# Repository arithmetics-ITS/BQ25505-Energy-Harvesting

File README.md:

# Breakout Board: BQ25505 ultra low-power energy harvester with battery management and autonomous power multiplexing
## Description

The bq25505 device is specifically designed to efficiently extract the microwatts (μW) to miliwatts (mW) of power generated from a variety of DC energy harvesting, high-impedance sources like photovoltaic (solar) or thermal electric generators (TEGs) without collapsing those sources. The batterymanagement features of the bq25505 ensure that a secondary rechargeable battery is not overcharged by this extracted power, with voltage boosted, nor depleted beyond safe limits by a system load. The
integrated multiplexer gate drivers autonomously switch the system load to a primary nonrechargeable battery if the secondary battery voltage falls below the user-defined VBAT_OK threshold.

## Features

- Texas Instruments BQ25505
- Designed for solar applications with MPPT
- 2x Dual, P-Channel, ChipFET 20 V, 4.1 A for primary and secondary battery switching
- 2x LEDs to visualize the currently used battery (PRI or SEC)

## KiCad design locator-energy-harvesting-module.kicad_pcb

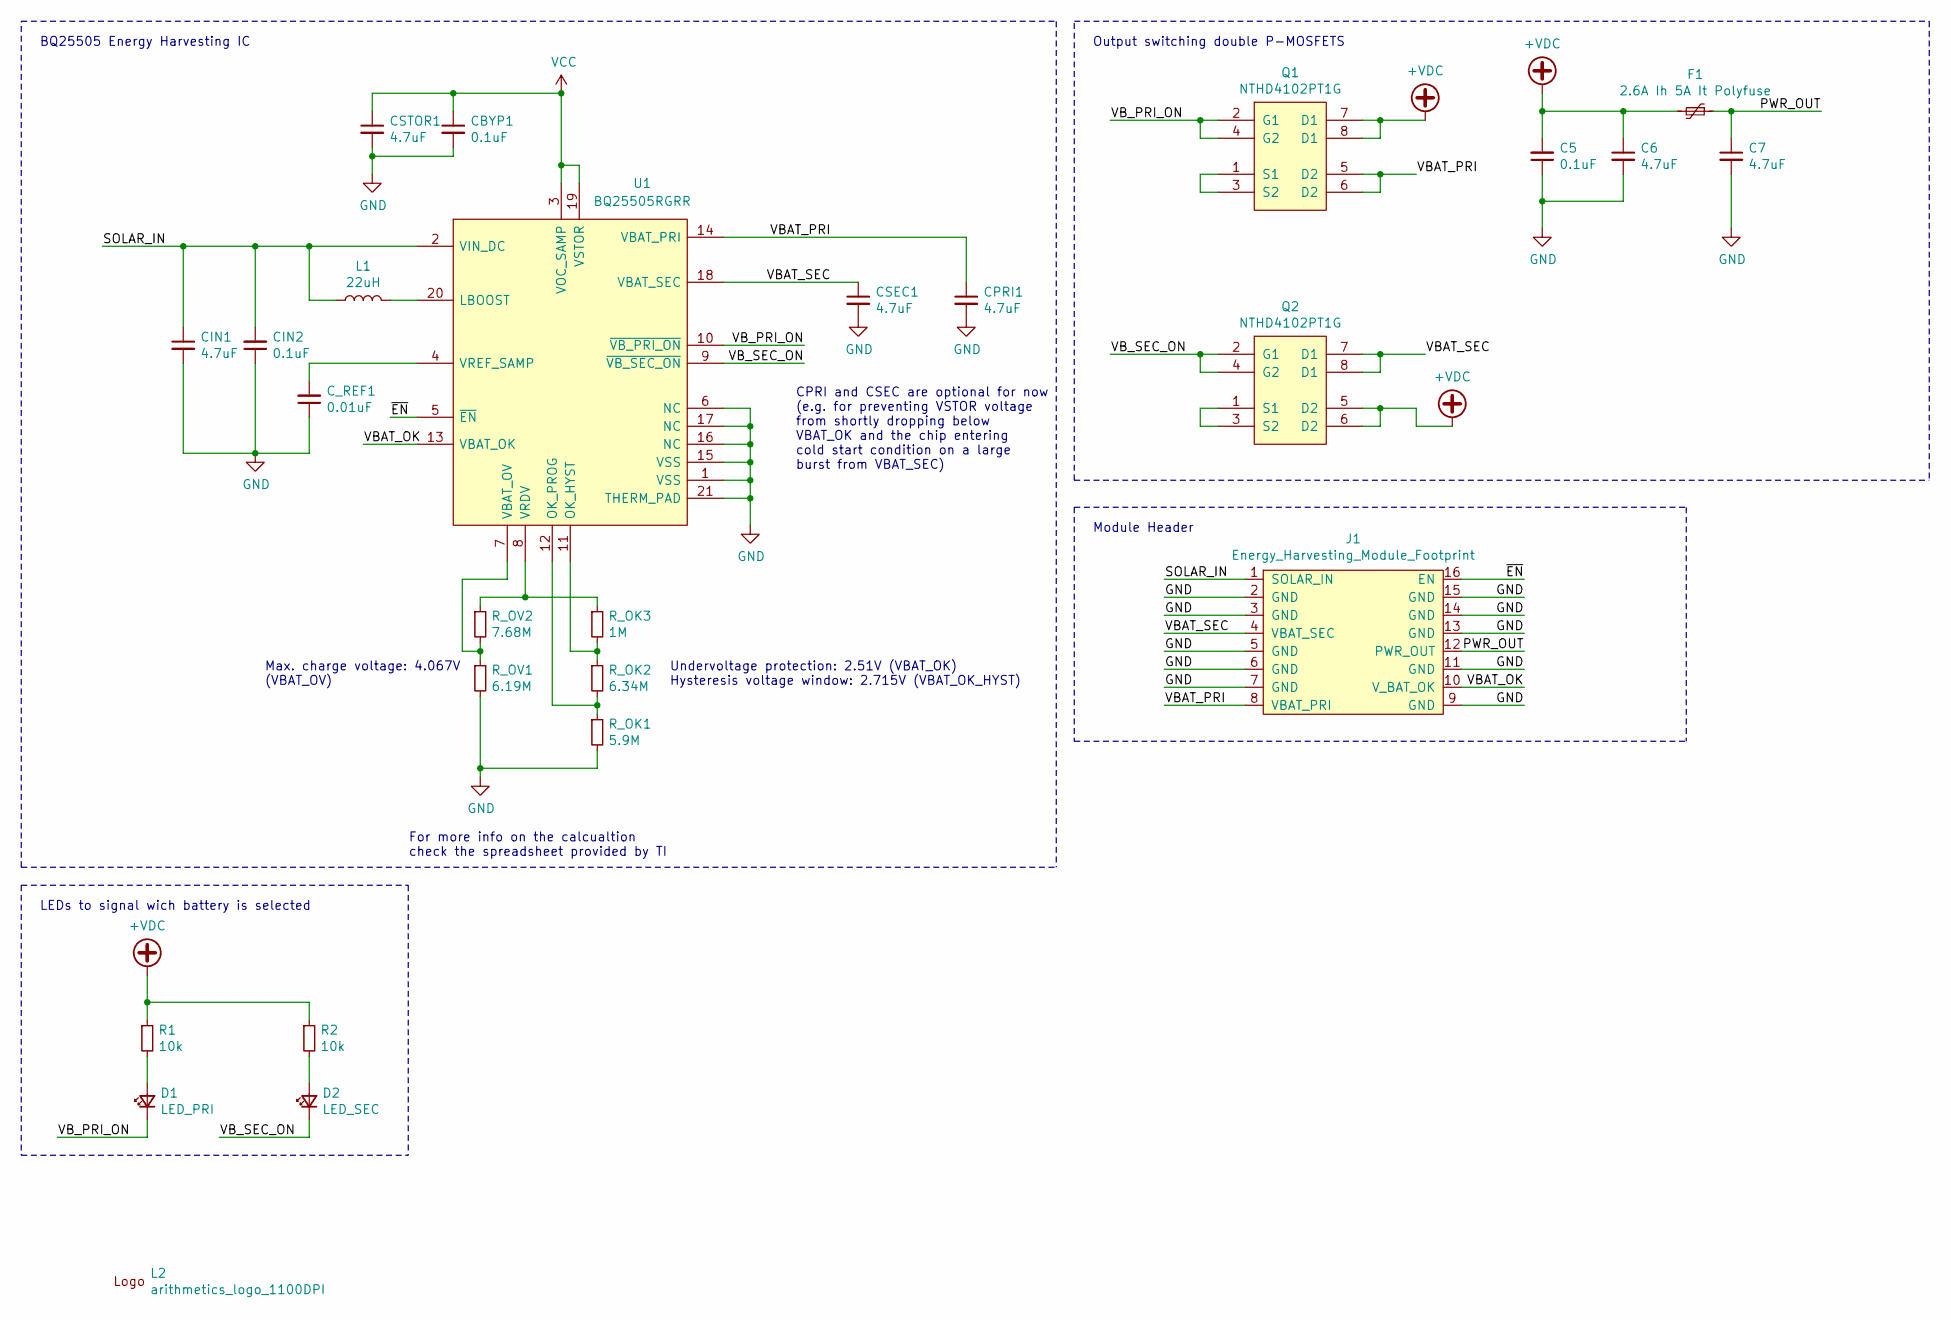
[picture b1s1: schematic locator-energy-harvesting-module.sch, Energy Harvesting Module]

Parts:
C5: 0.1uF; C_0603_1608Metric; MPN C0603X104J4RECAUTO
C6, C7: 4.7uF; C_0603_1608Metric; MPN C1608X5R1C475K080AC
CBYP1: 0.1uF; C_0603_1608Metric; MPN C0603X104J4RECAUTO
CIN1: 4.7uF; C_0603_1608Metric; MPN C1608X5R1C475K080AC
CIN2: 0.1uF; C_0603_1608Metric; MPN C0603X104J4RECAUTO
CPRI1: 4.7uF; C_0603_1608Metric; MPN C1608X5R1C475K080AC
CSEC1: 4.7uF; C_0603_1608Metric; MPN C1608X5R1C475K080AC
CSTOR1: 4.7uF; C_0603_1608Metric; MPN C1608X5R1C475K080AC
C_REF1: 0.01uF; C_0603_1608Metric; MPN GRM1885C1H103JA01D
D1: LED_PRI; LED_0603_1608Metric; MPN LS L29K-G1H2-1-Z
D2: LED_SEC; LED_0603_1608Metric; MPN LS L29K-G1H2-1-Z
F1: 2.6A Ih 5A It Polyfuse; Fuse_1812_4532Metric_Castellated; MPN 0ZCG0260FF2C
J1: Energy_Harvesting_Module_Footprint
L1: 22uH; L_Coilcraft_LPS4018; MPN LPS4018-223MRB
L2: arithmetics_logo_1100DPI; logo_1100_DPI
Q1, Q2: NTHD4102PT1G; NTHD4102P_ChipFET_CASE_1206A; MPN NTHD4102PT1G
R1, R2: 10k; R_0603_1608Metric; MPN AC0603JR-0710KL
R_OK1: 5.9M; R_0603_1608Metric; MPN CRCW06035M90FKEA
R_OK2: 6.34M; R_0603_1608Metric; MPN CRCW06036M34FKEA
R_OK3: 1M; R_0603_1608Metric; MPN AC0603FR-071ML
R_OV1: 6.19M; R_0603_1608Metric; MPN CRCW06036M19FKEA
R_OV2: 7.68M; R_0603_1608Metric; MPN CRCW06037M68FKEA
U1: BQ25505RGRR; BQ25505; MPN BQ25505RGRR

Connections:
+VDC: C5.2, C6.1, F1.2, Q1.7 (D1), Q1.8 (D1), Q2.5 (D2), Q2.6 (D2), R1.1, R2.1
/PWR_OUT: C7.1, F1.1, J1.12 (PWR_OUT)
/SOLAR_IN: CIN1.1, CIN2.2, J1.1 (SOLAR_IN), L1.1, U1.2 (VIN_DC)
/VBAT_OK: J1.10 (V_BAT_OK), U1.13 (VBAT_OK)
/VBAT_PRI: CPRI1.1, J1.8 (VBAT_PRI), Q1.5 (D2), Q1.6 (D2), U1.14 (VBAT_PRI)
/VBAT_SEC: CSEC1.1, J1.4 (VBAT_SEC), Q2.7 (D1), Q2.8 (D1), U1.18 (VBAT_SEC)
/VB_PRI_ON: D1.1 (K), Q1.2 (G1), Q1.4 (G2), U1.10 (~VB_PRI_ON)
/VB_SEC_ON: D2.1 (K), Q2.2 (G1), Q2.4 (G2), U1.9 (~VB_SEC_ON)
/~EN: J1.16 (EN), U1.5 (~EN)
GND: C5.1, C6.2, C7.2, CBYP1.2, CIN1.2, CIN2.1, CPRI1.2, CSEC1.2, CSTOR1.2, C_REF1.1, J1.2 (GND), J1.3 (GND), J1.5 (GND), J1.6 (GND), J1.7 (GND), J1.9 (GND), J1.11 (GND), J1.13 (GND), J1.14 (GND), J1.15 (GND), R_OK1.2, R_OV1.2, U1.1 (VSS), U1.6 (NC), U1.15 (VSS), U1.16 (NC), U1.17 (NC), U1.21 (THERM_PAD)
unnamed: C_REF1.2, U1.4 (VREF_SAMP)
unnamed: D1.2 (A), R1.2
unnamed: D2.2 (A), R2.2
unnamed: L1.2, U1.20 (LBOOST)
unnamed: Q1.1 (S1), Q1.3 (S2)
unnamed: Q2.1 (S1), Q2.3 (S2)
unnamed: R_OK1.1, R_OK2.2, U1.12 (OK_PROG)
unnamed: R_OK2.1, R_OK3.2, U1.11 (OK_HYST)
unnamed: R_OK3.1, R_OV2.1, U1.8 (VRDV)
unnamed: R_OV1.1, R_OV2.2, U1.7 (VBAT_OV)
VCC: CBYP1.1, CSTOR1.1, U1.3 (VOC_SAMP), U1.19 (VSTOR)

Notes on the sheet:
For more info on the calcualtion check the spreadsheet provided by TI
Module Header
Output switching double P-MOSFETS
BQ25505 Energy Harvesting IC
Max. charge voltage: 4.067V (VBAT_OV)
Undervoltage protection: 2.51V (VBAT_OK) Hysteresis voltage window: 2.715V (VBAT_OK_HYST)
CPRI and CSEC are optional for now (e.g. for preventing VSTOR voltage from shortly dropping below VBAT_OK and the chip entering cold start condition on a large burst from VBAT_SEC)
LEDs to signal wich battery is selected

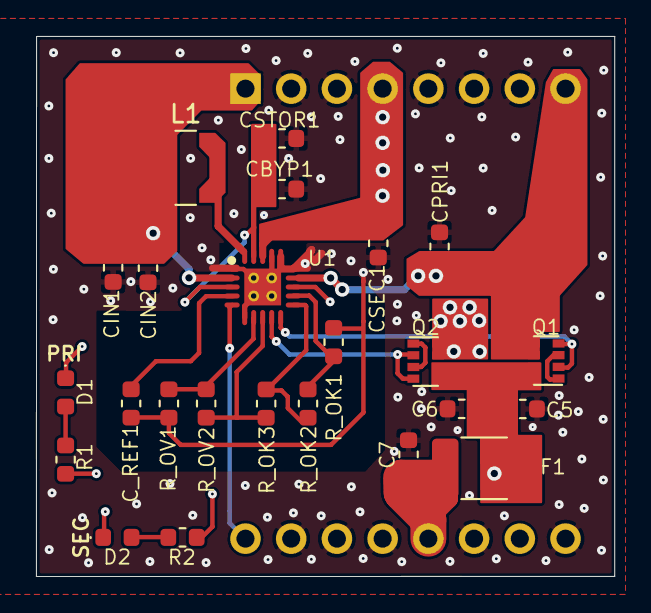
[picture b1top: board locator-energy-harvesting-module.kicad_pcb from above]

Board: 4 copper layers, 32.1 x 30.0 mm, 26 parts (1 on the bottom side), 21 nets.

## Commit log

2021-02-22 initial

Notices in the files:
locator-energy-harvesting-module.kicad_pcb:
(c) 2020 Arithmetics ITS
